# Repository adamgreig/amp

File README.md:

# Adam Magic Probe

A clone of the wonderful
[Black Magic Probe](http://www.blacksphere.co.nz/main/blackmagic) but in KiCAD 
and with a few small hardware tweaks.

As such this work is also distributed under the CC-BY-SA licence.

This is a really useful tool for ARM development and I'm incredibly grateful 
that it's open hardware and firmware. You should consider buying one!

## Changes From Black Magic Mini

* MicroUSB port
* No LEDs
* Cheaper, higher current LDO
* TagConnect for programming the host STM32

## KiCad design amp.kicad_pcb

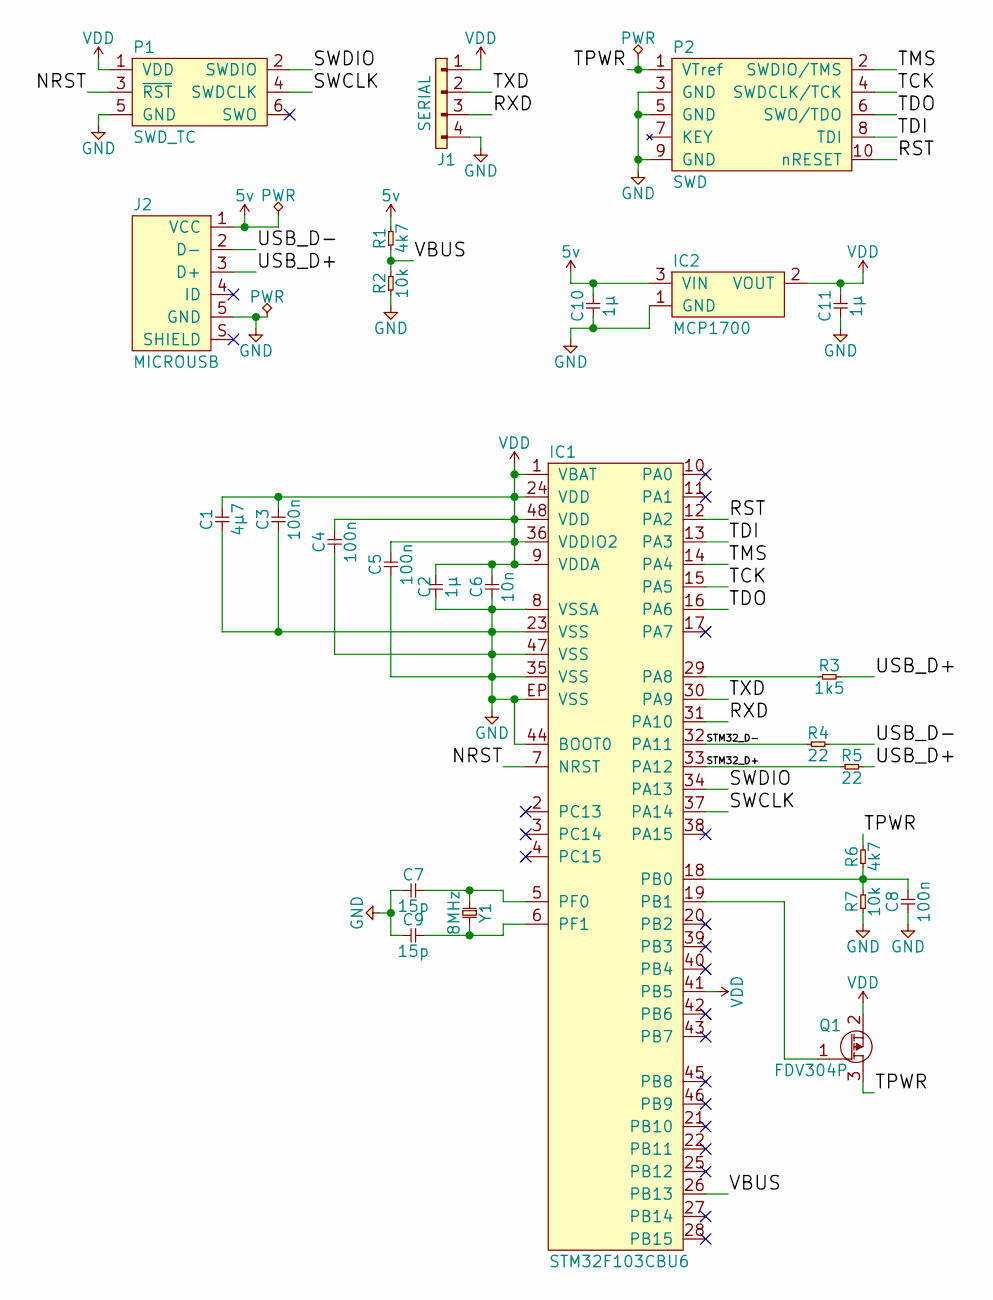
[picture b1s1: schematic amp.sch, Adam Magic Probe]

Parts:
C1: 4µ7; 0603
C2, C10, C11: 1µ; 0603
C3, C4, C5, C8: 100n; 0402
C6: 10n; 0402
C7, C9: 15p; 0402
IC1: STM32F103CBU6; QFN-48-EP-ST; Farnell 2060891
IC2: MCP1700; SOT-23; Farnell 1296592
J1: SERIAL; SM04B-PASS
J2: MICROUSB; MICROUSB_MOLEX_47589-0001; Farnell 1568023
P1: SWD_TC; TC2030-NL
P2: SWD; FTSH-105-01-L-DV-K
Q1: FDV304P; SOT-23; Farnell 9846123
R1, R6: 4k7; 0402
R2, R7: 10k; 0402
R3: 1k5; 0402
R4, R5: 22; 0402
Y1: 8MHz; XTAL-50x32; Farnell 2101329

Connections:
5v: C10.2, IC2.3 (VIN), J2.1 (VCC), R1.2
/NRST: IC1.7 (NRST), P1.3 (~RST)
/RST: IC1.12 (PA2), P2.10 (nRESET)
/RXD: IC1.31 (PA10), J1.3
/STM32_D+: IC1.33 (PA12), R5.1
/STM32_D-: IC1.32 (PA11), R4.1
/SWCLK: IC1.37 (PA14), P1.4 (SWDCLK)
/SWDIO: IC1.34 (PA13), P1.2 (SWDIO)
/TCK: IC1.15 (PA5), P2.4 (SWDCLK/TCK)
/TDI: IC1.13 (PA3), P2.8 (TDI)
/TDO: IC1.16 (PA6), P2.6 (SWO/TDO)
/TMS: IC1.14 (PA4), P2.2 (SWDIO/TMS)
/TPWR: P2.1 (VTref), Q1.3 (D), R6.2
/TXD: IC1.30 (PA9), J1.2
/USB_D+: J2.3 (D+), R3.2, R5.2
/USB_D-: J2.2 (D-), R4.2
/VBUS: IC1.26 (PB13), R1.1, R2.2
GND: C1.1, C2.1, C3.1, C4.1, C5.1, C6.1, C7.1, C8.1, C9.1, C10.1, C11.1, IC1.8 (VSSA), IC1.23 (VSS), IC1.35 (VSS), IC1.44 (BOOT0), IC1.47 (VSS), IC1.EP (VSS), IC2.1 (GND), J1.4, J2.5 (GND), P1.5 (GND), P2.3 (GND), P2.5 (GND), P2.9 (GND), R2.1, R7.1
unnamed: C7.2, IC1.5 (PF0), Y1.1
unnamed: C8.2, IC1.18 (PB0), R6.1, R7.2
unnamed: C9.2, IC1.6 (PF1), Y1.2
unnamed: IC1.19 (PB1), Q1.1 (G)
unnamed: IC1.29 (PA8), R3.1
VDD: C1.2, C2.2, C3.2, C4.2, C5.2, C6.2, C11.2, IC1.1 (VBAT), IC1.9 (VDDA), IC1.24 (VDD), IC1.36 (VDDIO2), IC1.41 (PB5), IC1.48 (VDD), IC2.2 (VOUT), J1.1, P1.1 (VDD), Q1.2 (S)

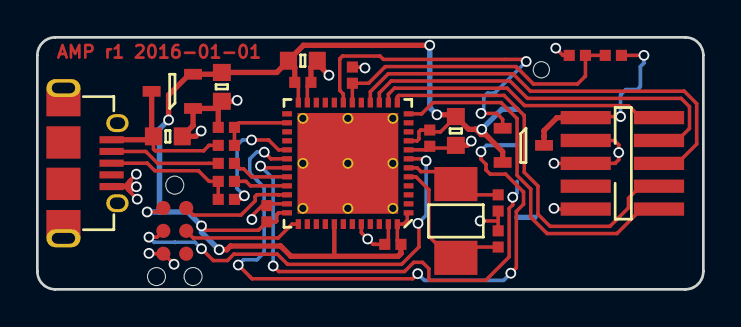
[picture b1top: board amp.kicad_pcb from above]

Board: 2 copper layers, 37.0 x 14.0 mm, 26 parts (1 on the bottom side), 24 nets.

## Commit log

2016-01-01 statement of intent
2016-01-01 First layout of schematic.
2016-01-01 Document changes from original
2016-01-01 Only need PB5 for version sensing
2016-01-01 Specify the PFET
2016-01-02 mostly routed go
2016-01-02 fully routed
2016-01-02 silk etc
2016-01-03 try swap to surface-mount swd connector
2016-01-03 ok, render gerbers for panel
2016-01-03 redo panel with new usb and jst connectors
2016-01-03 Add zip for manufacturing
2016-01-03 Add Farnell order codes
2016-01-24 add good single-board stencil

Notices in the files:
amp.sch:
Licence: CC-BY-SA
